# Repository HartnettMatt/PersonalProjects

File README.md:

# Personal Projects

## Introduction

Hello and welcome to my repo of personal projects! 

There are a quite a few projects that I've stored in here, and none are really that related to each other, but each hold a special place in my heart.

Please look around and mess with whatever you like to. Let me know if there are any issues or bugs.

## Project List

* AudioBalancer - All of my stuff for my version of the DEEJ audio balancer

* Cocotb - My experiments and learning with Cocotb, the python based FPGA verification toolset

* Fleet Run Configurations - Various run configs for JetBrain's Fleet IDE

* ESPHome - Custom smart home projects

## License

This repository is licensed under the MIT License. See the LICENSE file for details.

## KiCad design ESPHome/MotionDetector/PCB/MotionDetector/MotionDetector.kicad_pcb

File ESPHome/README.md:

# ESPHome Projects

This repository contains a collection of projects leveraging the ESP32 microcontroller and ESPHome integration with Home Assistant. Each project is organized as a standalone module, making it easy to explore and adapt for your own smart home setups.

## Project Structure

Each project in this repository follows the same directory structure for consistency and ease of navigation:

Config: Contains YAML configuration files used for ESPHome integration with Home Assistant.

Firmware: Includes any additional firmware files required for the specific project.

PCB: Houses PCB design files for hardware components of the project.

3D: Contains CAD files for any 3D-printed elements required by the project.

Docs: Any relevant documentation for the project.

## Current Projects

### MotionDetector

A motion detection system using ESP32 and ESPHome to seamlessly integrate with Home Assistant.

Features include:

* Real-time motion detection

* Customizable alerts through Home Assistant

## Getting Started

1. Clone this repo and navigate to the desired project folder

2. Flash the ESP32 with ESPHome as per ESPHome's documentation: https://esphome.io/guides/getting_started_hassio

* I've had the best experiance with plugging the ESP32 into the raspberry pi running HAOS

3. Install the ESPHome plug in

4. Configure the device with WiFi credentials and paste in yaml

5. Flash the device with the project yaml

6. Assemble and test

## Requirements

* ESPHome installed and configured

* ESP32 microcontroller

* Home Assistant OS instance

* Relevant hardware components (specific to each project)

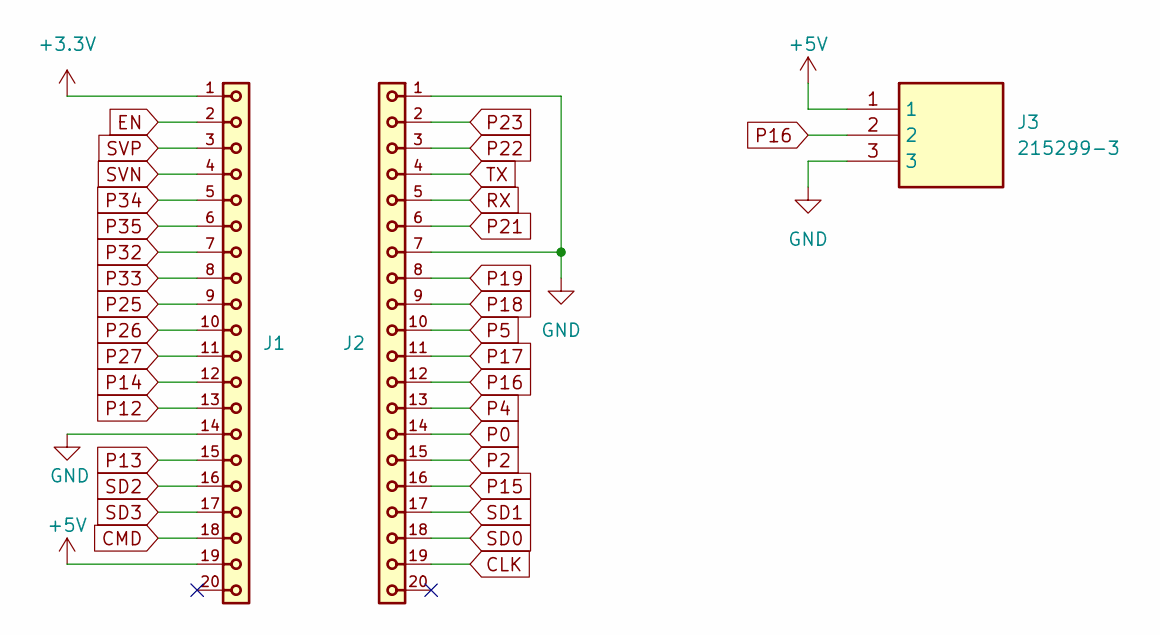
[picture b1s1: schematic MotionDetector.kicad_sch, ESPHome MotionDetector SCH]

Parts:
J1, J2: 61302011821; PART-NUMBER 61302011821
J3: 215299-3; SHDR3W78P0X254_1X3_772X252X850P; Mouser Part Number 571-215299-3

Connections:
+3.3V: J1.1
+5V: J1.19, J3.1
CLK: J2.19
CMD: J1.18
EN: J1.2
GND: J1.14, J2.1, J2.7, J3.3
P0: J2.14
P2: J2.15
P4: J2.13
P5: J2.10
P12: J1.13
P13: J1.15
P14: J1.12
P15: J2.16
P16: J2.12, J3.2
P17: J2.11
P18: J2.9
P19: J2.8
P21: J2.6
P22: J2.3
P23: J2.2
P25: J1.9
P26: J1.10
P27: J1.11
P32: J1.7
P33: J1.8
P34: J1.5
P35: J1.6
RX: J2.5
SD0: J2.18
SD1: J2.17
SD2: J1.16
SD3: J1.17
SVN: J1.4
SVP: J1.3
TX: J2.4

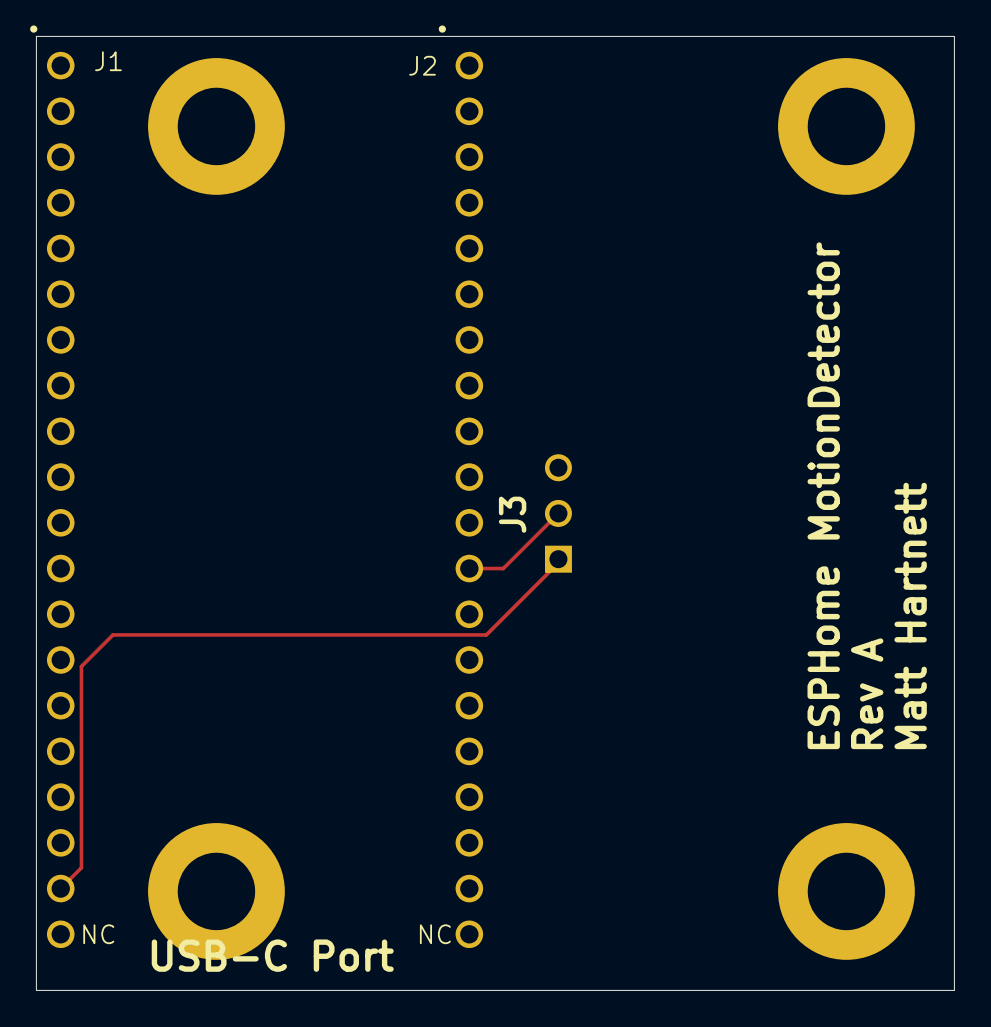
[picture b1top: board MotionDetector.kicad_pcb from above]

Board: 2 copper layers, 51.0 x 53.0 mm, 3 parts (0 on the bottom side), 3 nets.

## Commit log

2024-01-17 Initial commit of cocotb project
2024-01-19 Added generic monitor class
2024-01-19 Reformat
2024-01-19 Added my weirdly complicated Fleet runs
2024-01-30 Attempted to test AxiToAbp, ran into difficulties
2024-01-30 Attempted to compile AxiToAbp, was not sucessful
2024-01-30 Continued learning cocotb
2024-01-31 Continued development of testbench
2024-02-01 Made great progress, fully tested basic write sequence, found a couple bugs
2024-02-01 Ignoring verilator outputs
2024-02-01 Updated gitignore
2024-02-01 Working on read test
2024-07-17 Started software work on AudioBalancer project
2024-12-29 Added README and ESPHome
2024-12-29 Finished first revsion of the PCB for the motion detector project
2024-12-30 Cleaned up backups
2024-12-30 Began working on enclosure
2025-01-06 Added screw standoffs
2025-03-21 Finished some 3D printer designs
2025-05-09 Re-printed Toothbrush as one piece
2025-05-09 Finished up MotionDetector
2025-05-09 Added IRSender project, updated gitignore for better MacOS development
2025-05-13 Finished 3D print for IRSender, also makes a decent starting point for generic Arduino Nano mount
2025-05-15 Fixed second IR code for Max
2025-08-09 Started work on RGB Strip project
2025-08-11 Created my first Home Assistant project, an automation and python script to track and compute EV charging cost
2025-09-05 Started work on a CanvasBot that can hopefully help me backup files from Canvas and easily get class materials onto my local machine
2025-09-05 Updated CanvasBot so it can download files too, which is very helpful as a backup tool
2025-09-05 Modifided gitignore
2025-09-05 First commit of different resume formats, going to try some things out to find what works best for me
2025-09-05 Played around with resume stuff a bit more, think I'm going to do it mostly in HTML
2025-09-05 Finished first revision of full resume in HTML, going to delete other file formats
2025-09-05 Cleaned out other resumes
2025-09-05 Touched up a few things and created an FPGA-specific version of my resume
2025-09-08 Cleaned up some the text
2025-09-10 Updated formatting
2025-09-10 Tightend margins a bit
2025-09-10 Reverted back to old descriptions of jobs and projects, kept formatting changes
2025-09-10 Removed duplicate
2025-11-11 Designed a new full bathroom organizer
2025-11-11 Updated ev charging history
2025-11-11 Updated resume
2025-11-11 Re-exported resume
2025-11-16 Added some useful scripts that I keep handy
2025-11-21 Added a few things and re-organized
